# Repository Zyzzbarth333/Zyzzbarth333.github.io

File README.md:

# Zyzzbarth333.github.io

Personal portfolio site published with GitHub Pages at
[zyzzbarth333.github.io](https://zyzzbarth333.github.io). Plain HTML, CSS and a
little JavaScript, with no framework and nothing to build on Pages.

## Structure

| Path | Holds |
|---|---|
| `index.html` | Home: About Me, project cards, Experience, Contact |
| `projects/*.html` | One page per project, all on the same template |
| `404.html` | The not-found page Pages serves for a missing path |
| `assets/css/style.css` | All styles. Colours and fonts are tokens on `:root` |
| `assets/js/site.js` | Scroll fade-ins, and sizing for embedded figures |
| `assets/img/` | Profile photo, favicon and the card icons and figures under `projects/` |
| `assets/figures/` | Interactive figures (standalone pages), embedded in project pages |
| `assets/fonts/` | Self-hosted Fraunces and Sanchez, with their licences |
| `assets/vendor/` | Self-hosted three.js, Astronomy Engine and KiCanvas, with their licences |
| `assets/kicad/` | KiCad files shown by the KiCanvas viewer |
| `assets/models/` | STL files for the 3D viewer |
| `.nojekyll` | Tells Pages to serve the files as they are |

## Local preview

Serve the folder so paths resolve as they do on Pages:

    python3 -m http.server 8000

Then visit `http://localhost:8000`.

## Editing

- **Project pages** share one template: outcome, facts, lead figure, the
  problem, what was built, result, what went wrong, credits, then links to the
  next project. Team pages describe the author's own part and credit the team.
- **Cards** on the home page use inline isometric SVG icons drawn with the
  Anatomy kit (source and build script live outside this repo; the SVGs are in
  `assets/img/projects/*-icon.svg`). They animate on hover or keyboard focus,
  and stay still under `prefers-reduced-motion`.
- **Images** must have their metadata stripped before they are added (no
  EXIF, GPS or XMP). Resize them for the web first; figures are about
  1600 px wide and card icons are SVG.
- **Links** to other sites use `target="_blank"` with `rel="noopener"`.

## Deployment

Pushing to `main` publishes through GitHub Pages (Settings, then Pages,
source `main`, root). Allow about a minute for the build.

## Licence

Copyright (c) Isaac Johan Ziebarth. All rights reserved. The code and content of
this site are not licensed for reuse.

Third-party parts keep their own licences:

- `assets/figures/weather-station-exploded.html`, the card icons and
  `assets/css/iso-kit.css`: drawn and styled with the Anatomy kit, whose code is
  under the MIT License (`assets/figures/LICENSE-anatomy-kit.txt`).
- `assets/figures/osiris-v0-ibom.html`: generated by InteractiveHtmlBom (MIT License).
- `assets/vendor/three-0.187.0/`: three.js and five of its addons (MIT License, `LICENSE` beside
  them), minified copies used by `assets/figures/camera-mount-3d.html` and
  `assets/figures/havoc2-flight3d.html`.
- `assets/vendor/astronomy-engine-2.1.19/`: Astronomy Engine (MIT License, `LICENSE` beside it),
  used by the orrery page and its porkchop figure.
- `assets/vendor/kicanvas/`: KiCanvas (MIT License, `LICENSE.md` beside it), the KiCad viewer on the OSIRIS
  page, from kicanvas.org. This copy points its font stylesheet at `fonts/`, self-hosted: Material Symbols
  Outlined cut down to the icons KiCanvas uses (Apache License 2.0) and Nunito (SIL Open Font License), each
  with its licence.
- `assets/kicad/osiris-v0/`: the OSIRIS V0 KiCad project, board and schematic sheets, shown by that viewer.
- Fonts and libraries are all served from this repo. The one outside request is the visitor count:
  GoatCounter's counter script (`gc.zgo.at/count.js`) sends each page view to
  `zyzzbarth333.goatcounter.com`, with no cookies and no personal data stored. Embedded figures are not
  counted, and local previews are not counted either.
- Fonts in `assets/fonts/`: Fraunces and Sanchez, under the SIL Open Font License (the
  licence texts are beside them).
- Header icons: GitHub and Printables marks from Simple Icons (CC0); LinkedIn mark
  from Font Awesome Free (CC BY 4.0).
  The MakerWorld mark is MakerWorld's own (from its site header), used only to link
  to the author's MakerWorld profile; it remains MakerWorld's trademark.

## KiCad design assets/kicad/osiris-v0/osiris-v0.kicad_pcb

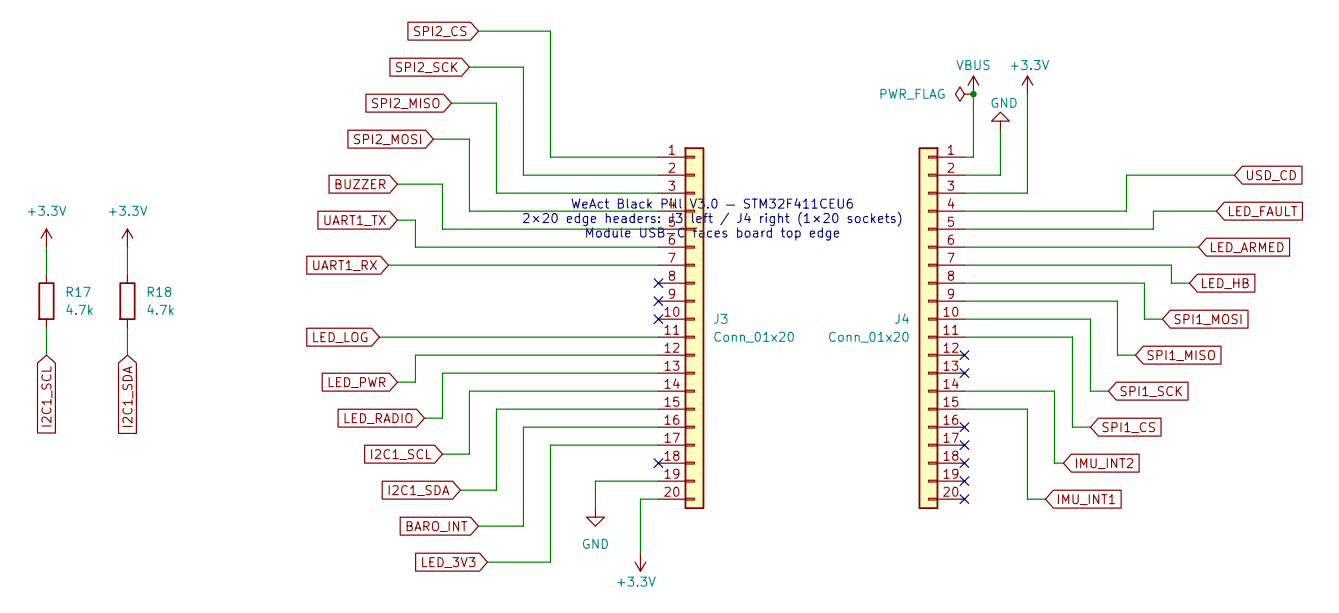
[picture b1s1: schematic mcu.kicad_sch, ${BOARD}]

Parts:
J3, J4: Conn_01x20; PinSocket_1x20_P2.54mm_Vertical
R17, R18: 4.7k; R_0603_1608Metric_Pad0.98x0.95mm_HandSolder

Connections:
+3.3V: J3.20, J4.3, R17.1, R18.1; also elsewhere on the board
BARO_INT: J3.16; also elsewhere on the board
BUZZER: J3.5; also elsewhere on the board
GND: J3.19, J4.2; also elsewhere on the board
I2C1_SCL: J3.14, R17.2; also elsewhere on the board
I2C1_SDA: J3.15, R18.2; also elsewhere on the board
IMU_INT1: J4.15; also elsewhere on the board
IMU_INT2: J4.14; also elsewhere on the board
LED_3V3: J3.17; also elsewhere on the board
LED_ARMED: J4.6; also elsewhere on the board
LED_FAULT: J4.5; also elsewhere on the board
LED_HB: J4.7; also elsewhere on the board
LED_LOG: J3.11; also elsewhere on the board
LED_PWR: J3.12; also elsewhere on the board
LED_RADIO: J3.13; also elsewhere on the board
SPI1_CS: J4.11; also elsewhere on the board
SPI1_MISO: J4.9; also elsewhere on the board
SPI1_MOSI: J4.8; also elsewhere on the board
SPI1_SCK: J4.10; also elsewhere on the board
SPI2_CS: J3.1; also elsewhere on the board
SPI2_MISO: J3.3; also elsewhere on the board
SPI2_MOSI: J3.4; also elsewhere on the board
SPI2_SCK: J3.2; also elsewhere on the board
UART1_RX: J3.7; also elsewhere on the board
UART1_TX: J3.6; also elsewhere on the board
USD_CD: J4.4; also elsewhere on the board
VBUS: J4.1; also elsewhere on the board

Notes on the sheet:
WeAct Black Pill V3.0 — STM32F411CEU6 2×20 edge headers: J3 left / J4 right (1×20 sockets) Module USB-C faces board top edge

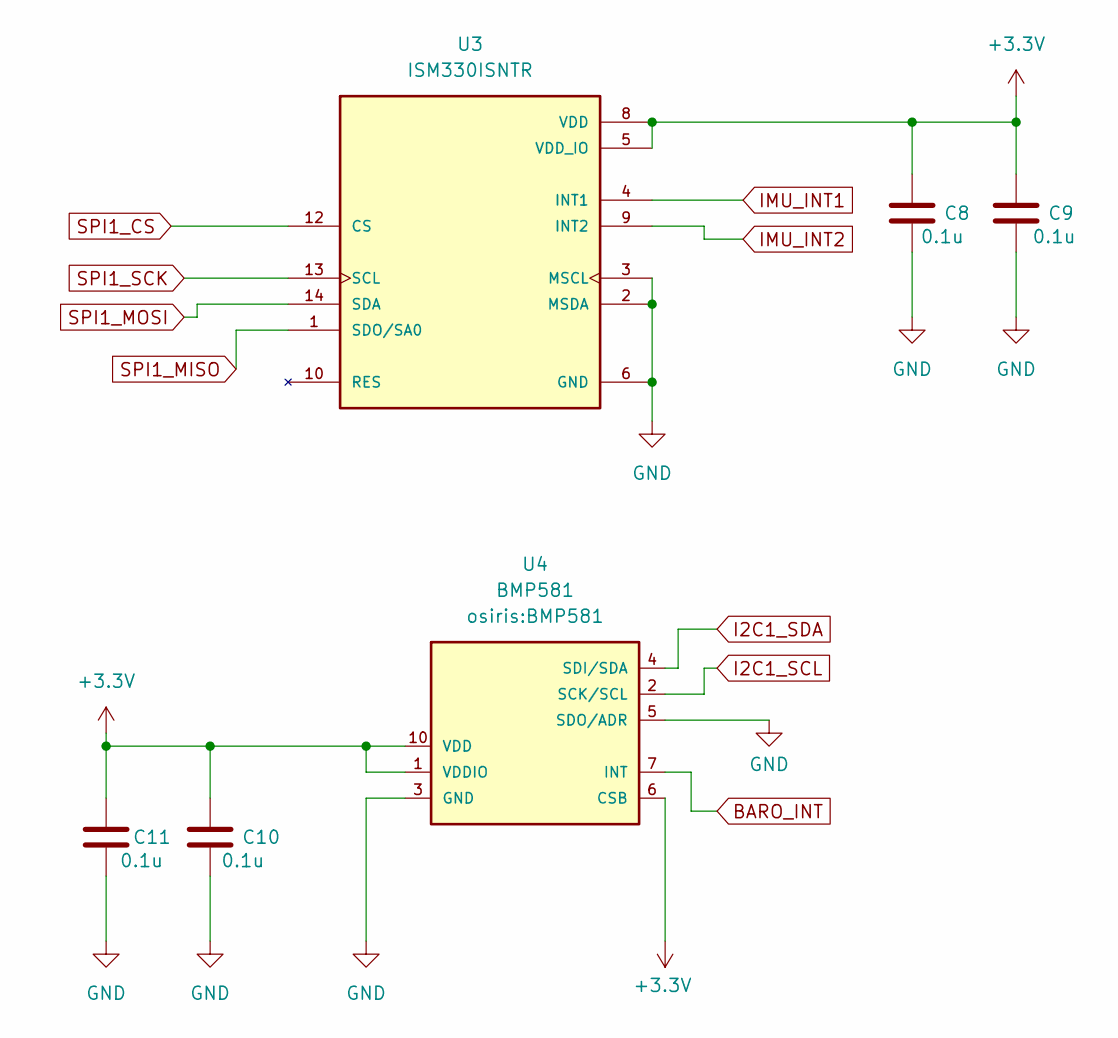
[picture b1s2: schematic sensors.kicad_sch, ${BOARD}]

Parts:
C8, C9, C10, C11: 0.1u; C_0603_1608Metric_Pad1.08x0.95mm_HandSolder
U3: ISM330ISNTR; LGA-14L_2P59X3P1X0P5_STM-M; PARTREV 2
U4: BMP581; MPN BMP581

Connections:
+3.3V: C8.1, C9.1, C10.1, C11.1, U3.5 (VDD_IO), U3.8 (VDD), U4.1 (VDDIO), U4.6 (CSB), U4.10 (VDD); also elsewhere on the board
BARO_INT: U4.7 (INT); also elsewhere on the board
GND: C8.2, C9.2, C10.2, C11.2, U3.2 (MSDA), U3.3 (MSCL), U3.6 (GND), U3.7 (GND), U4.3 (GND), U4.5 (SDO/ADR), U4.8 (GND), U4.9 (GND); also elsewhere on the board
I2C1_SCL: U4.2 (SCK/SCL); also elsewhere on the board
I2C1_SDA: U4.4 (SDI/SDA); also elsewhere on the board
IMU_INT1: U3.4 (INT1); also elsewhere on the board
IMU_INT2: U3.9 (INT2); also elsewhere on the board
SPI1_CS: U3.12 (CS); also elsewhere on the board
SPI1_MISO: U3.1 (SDO/SA0); also elsewhere on the board
SPI1_MOSI: U3.14 (SDA); also elsewhere on the board
SPI1_SCK: U3.13 (SCL); also elsewhere on the board

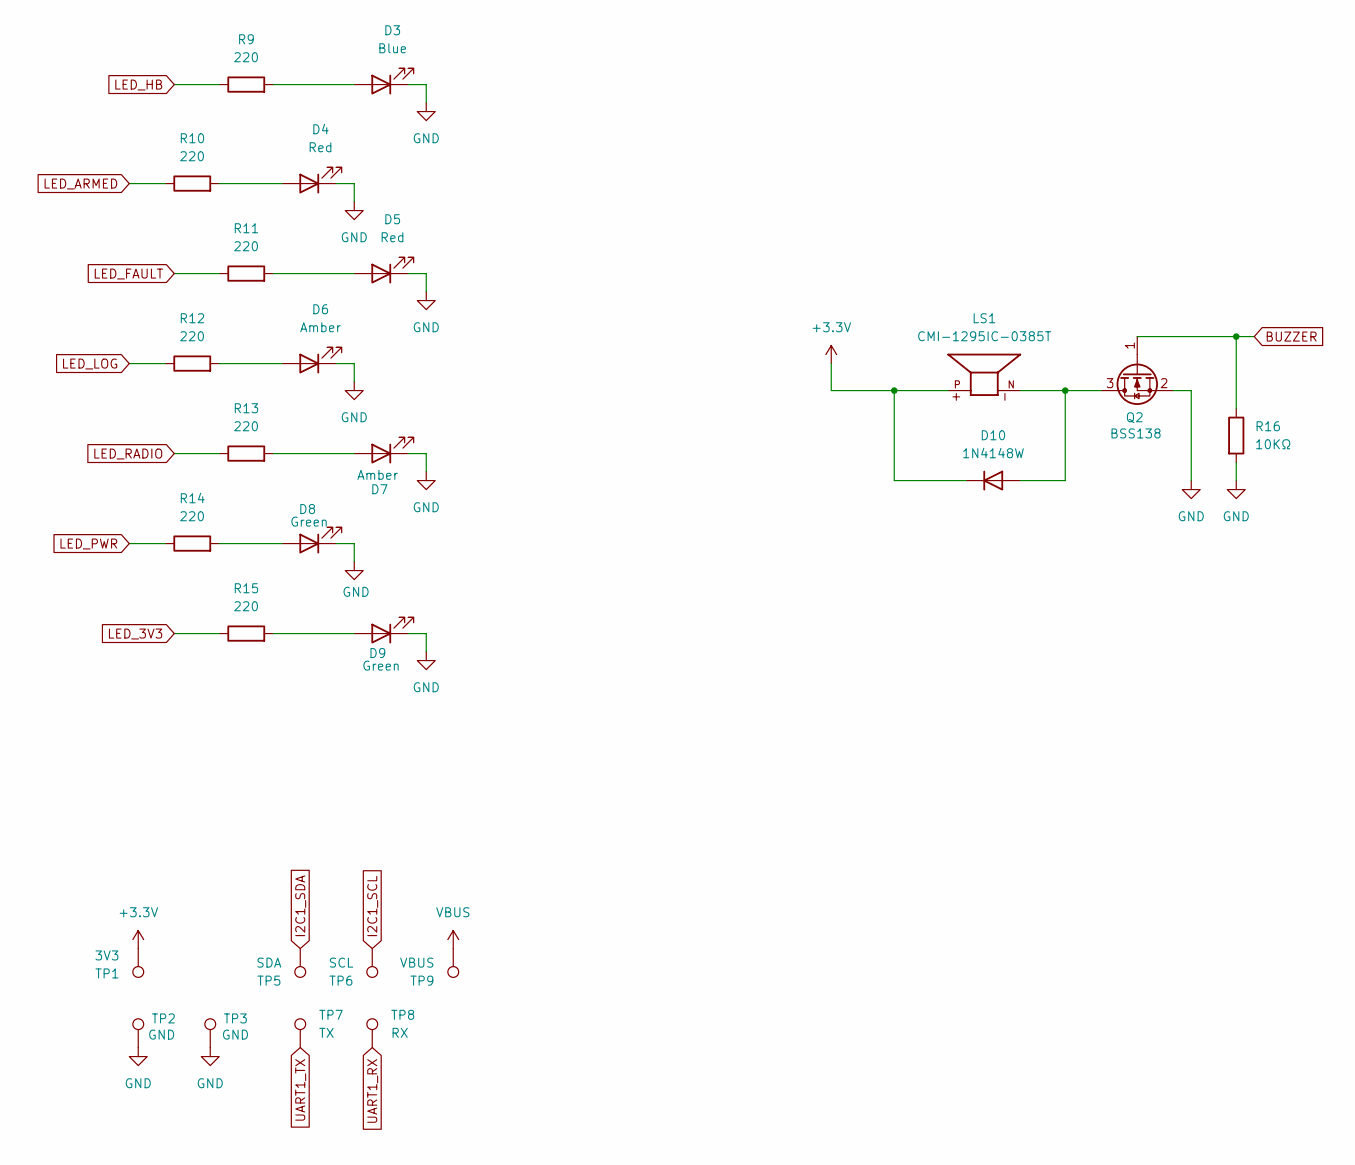
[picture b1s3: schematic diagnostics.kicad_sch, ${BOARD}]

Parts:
D3: Blue; LED_0603_1608Metric_Pad1.05x0.95mm_HandSolder; MPN LTST-C190TBKT
D4, D5: Red; LED_0603_1608Metric_Pad1.05x0.95mm_HandSolder; MPN LTST-C190KRKT
D6, D7: Amber; LED_0603_1608Metric_Pad1.05x0.95mm_HandSolder; MPN LTST-C190AKT
D8, D9: Green; LED_0603_1608Metric_Pad1.05x0.95mm_HandSolder; MPN LTST-C190KGKT
D10: 1N4148W; D_SOD-123
LS1: CMI-1295IC-0385T; CUI_CMI-1295IC-0385T; PARTREV 1.0
Q2: BSS138; SOT-23
R9, R10, R11, R12, R13, R14, R15: 220; R_0603_1608Metric_Pad0.98x0.95mm_HandSolder
R16: 10KΩ; R_0603_1608Metric_Pad0.98x0.95mm_HandSolder
TP1: 3V3; TestPoint_Pad_D1.5mm
TP2, TP3: GND; TestPoint_Pad_D1.5mm
TP5: SDA; TestPoint_Pad_D1.5mm
TP6: SCL; TestPoint_Pad_D1.5mm
TP7: TX; TestPoint_Pad_D1.5mm
TP8: RX; TestPoint_Pad_D1.5mm
TP9: VBUS; TestPoint_Pad_D1.5mm

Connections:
+3.3V: D10.1 (K), LS1.P, TP1.1 (1_1); also elsewhere on the board
BUZZER: Q2.1 (G), R16.1; also elsewhere on the board
GND: D3.1 (K), D4.1 (K), D5.1 (K), D6.1 (K), D7.1 (K), D8.1 (K), D9.1 (K), Q2.2 (S), R16.2, TP2.1 (1_1), TP3.1 (1_1); also elsewhere on the board
I2C1_SCL: TP6.1 (1_1); also elsewhere on the board
I2C1_SDA: TP5.1 (1_1); also elsewhere on the board
LED_3V3: R15.1; also elsewhere on the board
LED_ARMED: R10.1; also elsewhere on the board
LED_FAULT: R11.1; also elsewhere on the board
LED_HB: R9.1; also elsewhere on the board
LED_LOG: R12.1; also elsewhere on the board
LED_PWR: R14.1; also elsewhere on the board
LED_RADIO: R13.1; also elsewhere on the board
unnamed: D3.2 (A), R9.2
unnamed: D4.2 (A), R10.2
unnamed: D5.2 (A), R11.2
unnamed: D6.2 (A), R12.2
unnamed: D7.2 (A), R13.2
unnamed: D8.2 (A), R14.2
unnamed: D9.2 (A), R15.2
unnamed: D10.2 (A), LS1.N, Q2.3 (D)
UART1_RX: TP8.1 (1_1); also elsewhere on the board
UART1_TX: TP7.1 (1_1); also elsewhere on the board
VBUS: TP9.1 (1_1); also elsewhere on the board

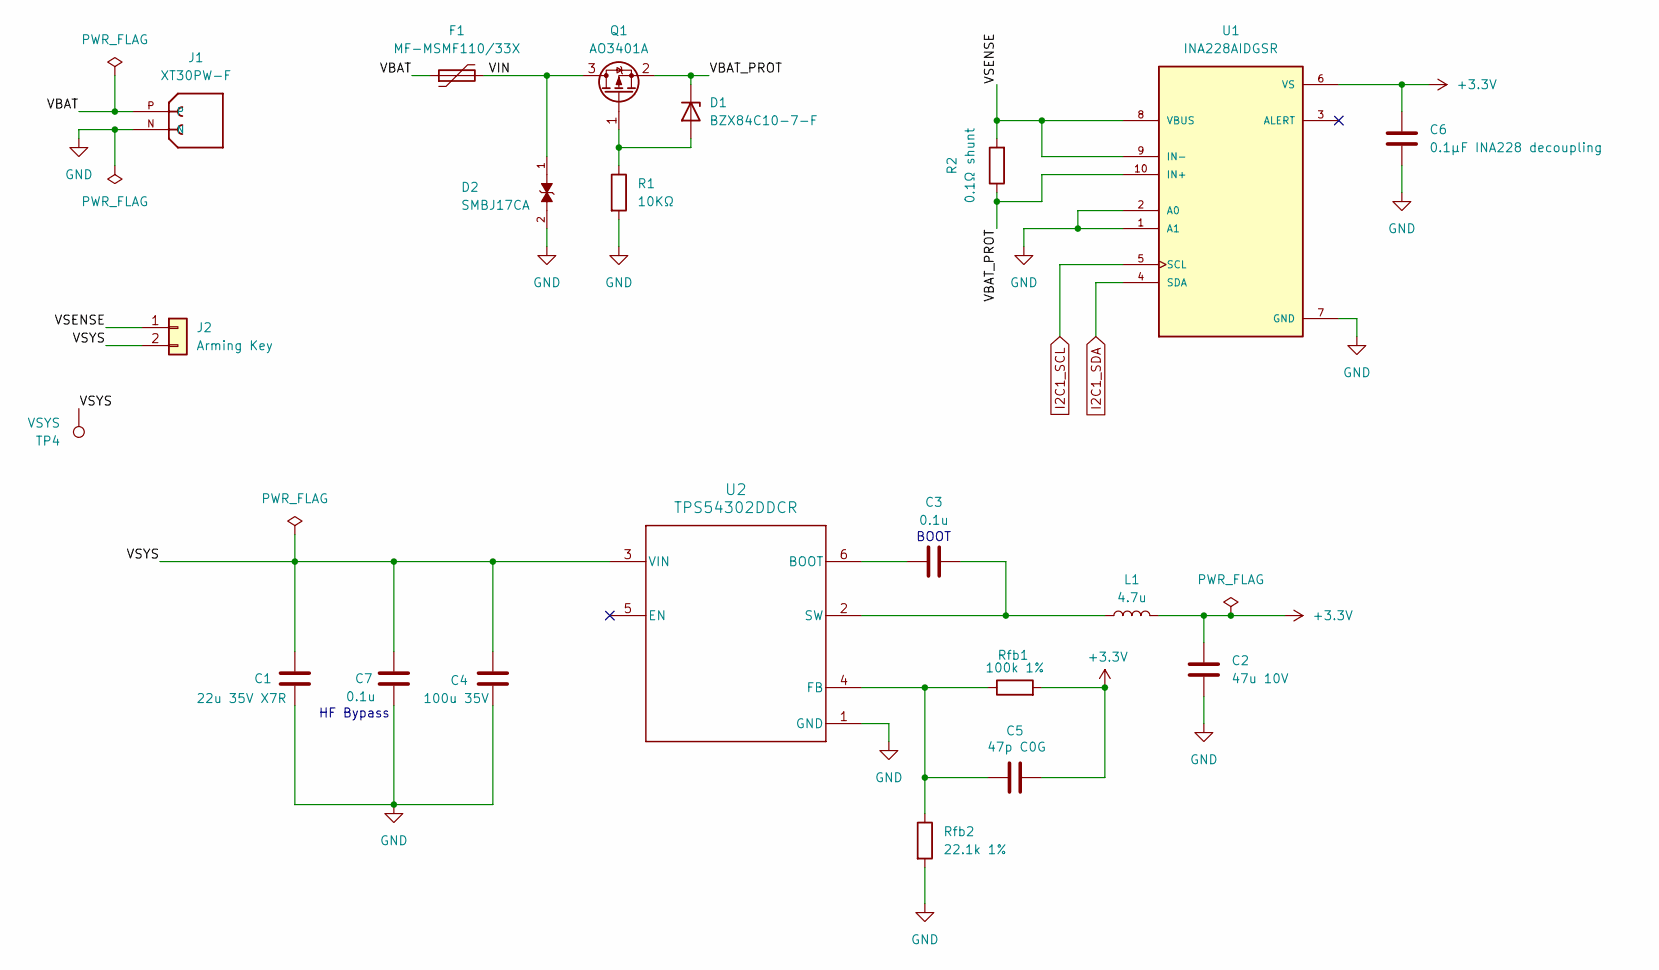
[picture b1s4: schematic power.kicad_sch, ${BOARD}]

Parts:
C1: 22u 35V X7R; C_1210_3225Metric_Pad1.33x2.70mm_HandSolder
C2: 47u 10V; C_0805_2012Metric_Pad1.18x1.45mm_HandSolder
C3, C7: 0.1u; C_0603_1608Metric_Pad1.08x0.95mm_HandSolder
C4: 100u 35V; C_Elec_6.3x7.7
C5: 47p C0G; C_0603_1608Metric_Pad1.08x0.95mm_HandSolder
C6: 0.1µF INA228 decoupling; C_0603_1608Metric_Pad1.08x0.95mm_HandSolder
D1: BZX84C10-7-F; SOT-23
D2: SMBJ17CA; DIOM4336X265N; PARTREV I2102
F1: MF-MSMF110/33X; Fuse_1812_4532Metric_Pad1.30x3.40mm_HandSolder; MPN MF-MSMF110/33X
J1: XT30PW-F; AMASS_XT30PW-F; PARTREV 1.2
J2: Arming Key; PinHeader_1x02_P2.54mm_Vertical
L1: 4.7u; IND_IHLP-2525CZ_VIS-M; MPN IHLP2525CZER4R7M11
Q1: AO3401A; SOT-23
R1: 10KΩ; R_0603_1608Metric_Pad0.98x0.95mm_HandSolder
R2: 0.1Ω shunt; R_2512_6332Metric_Pad1.40x3.35mm_HandSolder
Rfb1: 100k 1%; R_0603_1608Metric_Pad0.98x0.95mm_HandSolder
Rfb2: 22.1k 1%; R_0603_1608Metric_Pad0.98x0.95mm_HandSolder
TP4: VSYS; TestPoint_Pad_D1.5mm
U1: INA228AIDGSR; SOP50P490X110-10N; PARTREV A
U2: TPS54302DDCR; DDC0006A_M; MPN TPS54302DDCR

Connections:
+3.3V: C2.1, C5.2, C6.1, L1.2, Rfb1.2, U1.6 (VS); also elsewhere on the board
/Power/VBAT: F1.1, J1.P
/Power/VBAT_PROT: D1.3 (K), Q1.2 (S), R2.1, U1.10 (IN+)
/Power/VIN: D2.1, F1.2, Q1.3 (D)
/Power/VSENSE: J2.1, R2.2, U1.8 (VBUS), U1.9 (IN-)
/Power/VSYS: C1.1, C4.1, C7.1, J2.2, TP4.1 (1_1), U2.3 (VIN)
GND: C1.2, C2.2, C4.2, C6.2, C7.2, D2.2, J1.N, R1.2, Rfb2.2, U1.1 (A1), U1.2 (A0), U1.7 (GND), U2.1 (GND); also elsewhere on the board
I2C1_SCL: U1.5 (SCL); also elsewhere on the board
I2C1_SDA: U1.4 (SDA); also elsewhere on the board
unnamed: D1.1 (A), Q1.1 (G), R1.1
unnamed: C3.1, U2.6 (BOOT)
unnamed: C5.1, Rfb1.1, Rfb2.1, U2.4 (FB)
unnamed: C3.2, L1.1, U2.2 (SW)

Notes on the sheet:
HF Bypass
BOOT

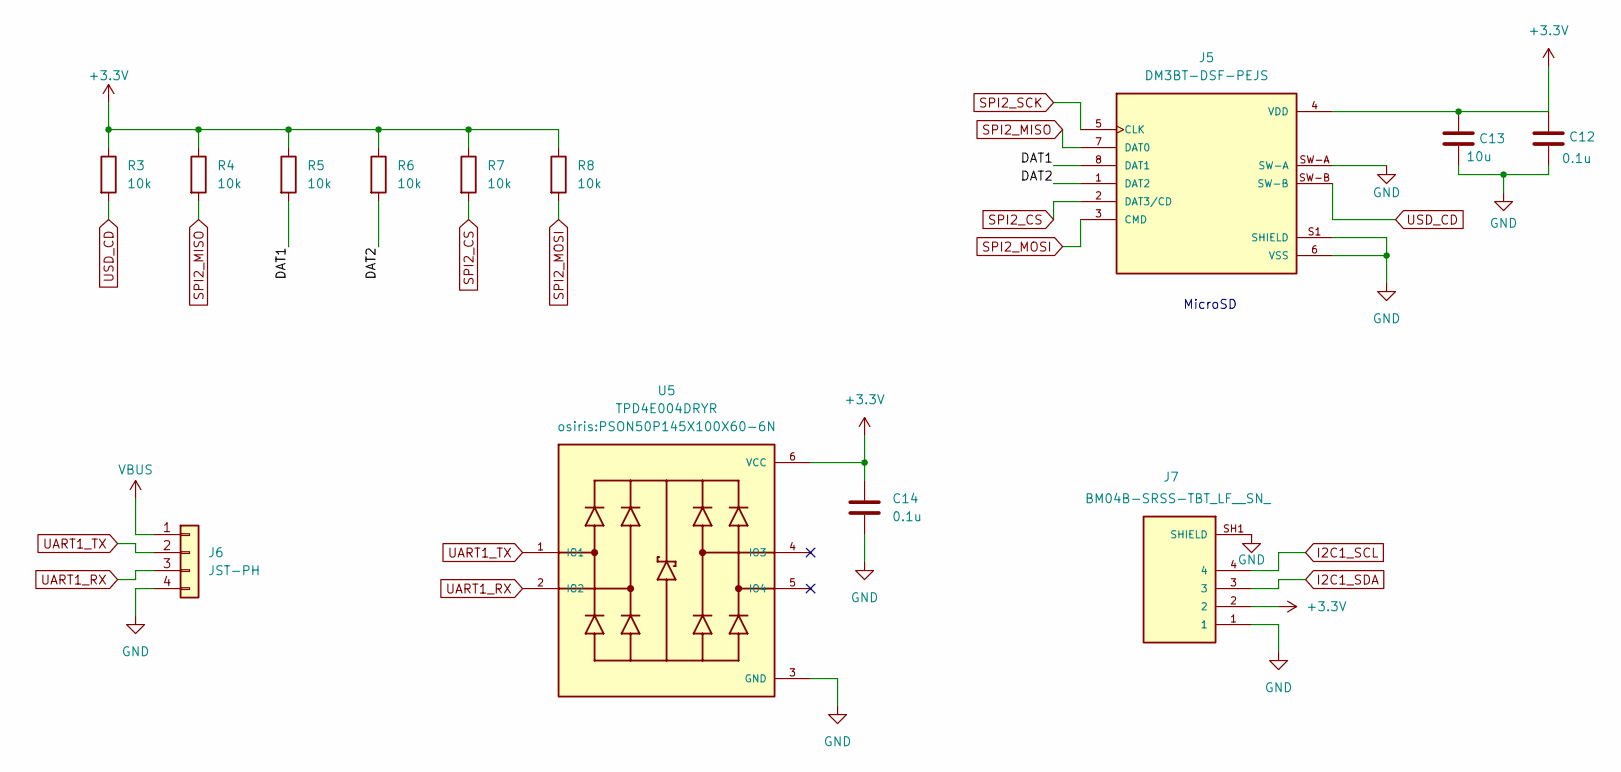
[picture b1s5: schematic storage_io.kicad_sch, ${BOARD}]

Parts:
C12, C14: 0.1u; C_0603_1608Metric_Pad1.08x0.95mm_HandSolder
C13: 10u; C_0805_2012Metric_Pad1.18x1.45mm_HandSolder
J5: DM3BT-DSF-PEJS; HRS_DM3BT-DSF-PEJS; MPN DM3BT-DSF-PEJS
J6: JST-PH; JST_PH_B4B-PH-K_1x04_P2.00mm_Vertical
J7: BM04B-SRSS-TBT_LF__SN_; CONN_BM04B-SRSS-TBT_LF__SN_; MPN BM04B-SRSS-TBT(LF)(SN)
R3, R4, R5, R6, R7, R8: 10k; R_0603_1608Metric_Pad0.98x0.95mm_HandSolder
U5: TPD4E004DRYR; PSON50P145X100X60-6N; MPN TPD4E004DRYR

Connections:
+3.3V: C12.1, C13.1, C14.1, J5.4 (VDD), J7.2, R3.1, R4.1, R5.1, R6.1, R7.1, R8.1, U5.6 (VCC); also elsewhere on the board
/Storage & IO/DAT1: J5.8 (DAT1), R5.2
/Storage & IO/DAT2: J5.1 (DAT2), R6.2
GND: C12.2, C13.2, C14.2, J5.6 (VSS), J5.S1 (SHIELD), J5.S2 (SHIELD), J5.S3 (SHIELD), J5.S4 (SHIELD), J5.SW-A, J6.4, J7.1, J7.SH1 (SHIELD), J7.SH2 (SHIELD), U5.3 (GND); also elsewhere on the board
I2C1_SCL: J7.4; also elsewhere on the board
I2C1_SDA: J7.3; also elsewhere on the board
SPI2_CS: J5.2 (DAT3/CD), R7.2; also elsewhere on the board
SPI2_MISO: J5.7 (DAT0), R4.2; also elsewhere on the board
SPI2_MOSI: J5.3 (CMD), R8.2; also elsewhere on the board
SPI2_SCK: J5.5 (CLK); also elsewhere on the board
UART1_RX: J6.3, U5.2 (IO2); also elsewhere on the board
UART1_TX: J6.2, U5.1 (IO1); also elsewhere on the board
USD_CD: J5.SW-B, R3.2; also elsewhere on the board
VBUS: J6.1; also elsewhere on the board

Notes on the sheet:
MicroSD

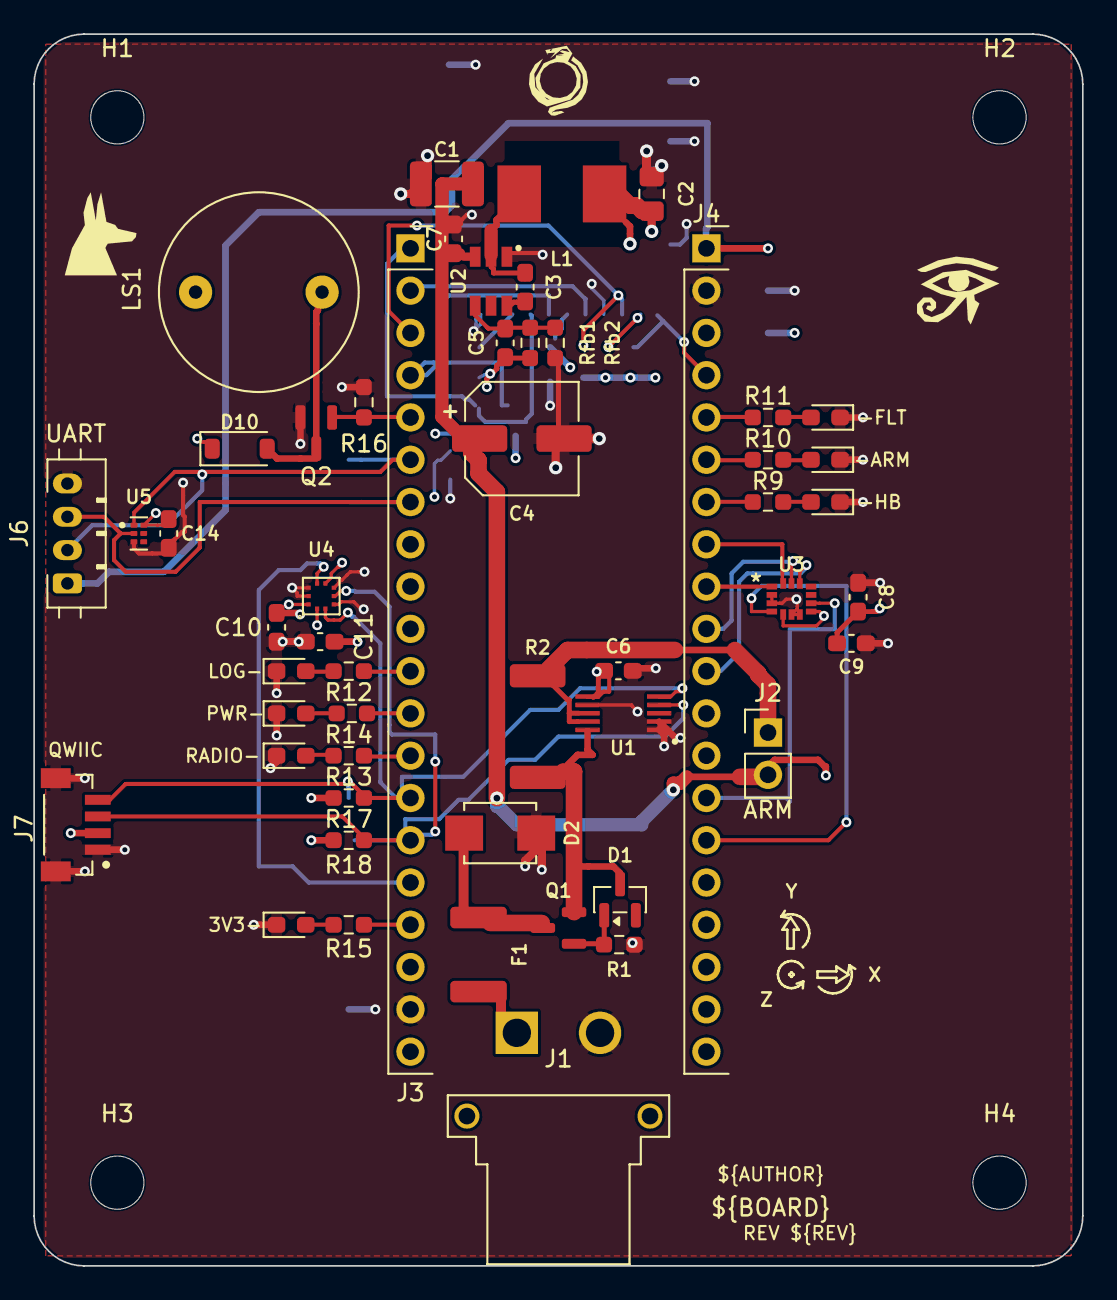
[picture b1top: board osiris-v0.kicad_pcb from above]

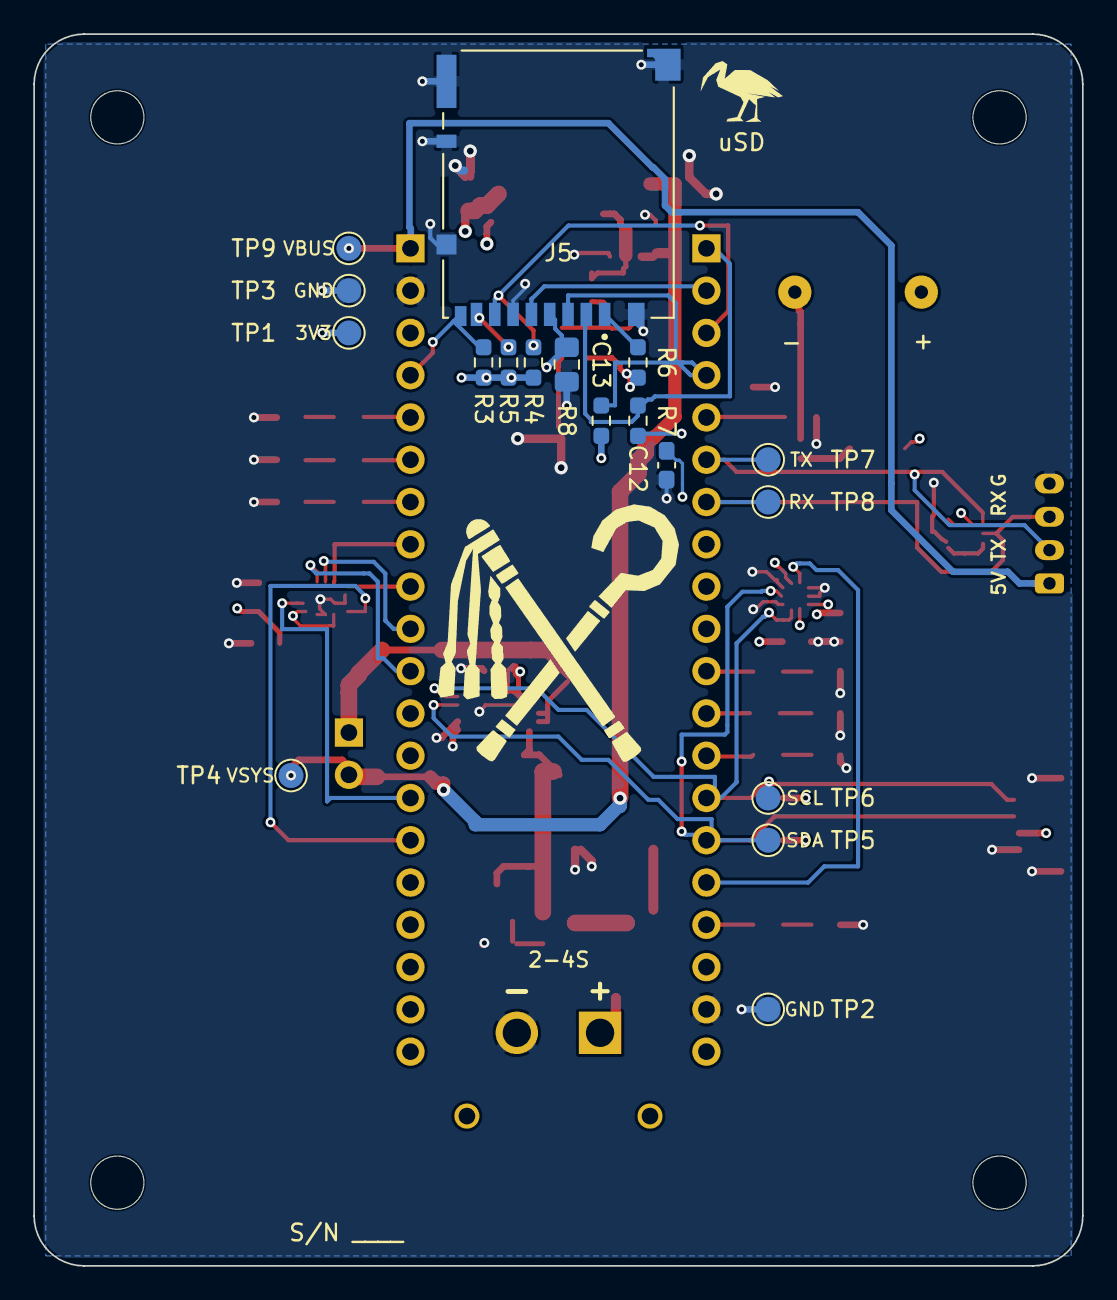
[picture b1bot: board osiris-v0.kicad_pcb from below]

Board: 4 copper layers, 63.0 x 74.0 mm, 81 parts (19 on the bottom side), 46 nets.

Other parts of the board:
AX1, AX2: SILK-Axis-ArrowCurl
AX3: SILK-Axis-Z
G1: SILK-God-Ra
G2: SILK-God-Thoth
G3: SILK-God-Horus
G4: SILK-God-Anubis
H1, H2, H3, H4: MountingHole_3.2mm_M3

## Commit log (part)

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2024-07-30 Rename assets/css/style.css to style.css
2024-07-30 Rename style.css to styles.css
2024-07-30 Rename styles.css to style.css
2024-07-30 Rename style.css to assets/css/style.css
2024-07-30 moving css path
2024-07-30 Update Navigation Bar
